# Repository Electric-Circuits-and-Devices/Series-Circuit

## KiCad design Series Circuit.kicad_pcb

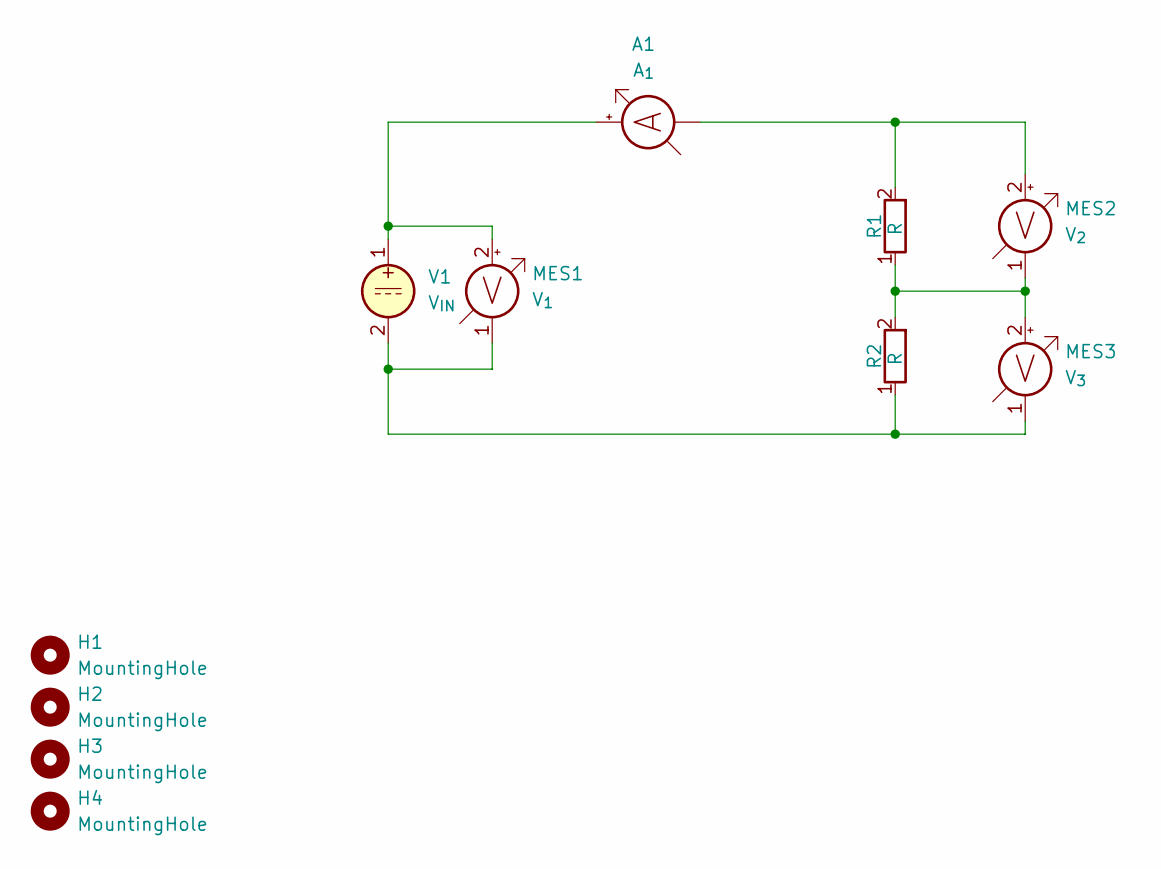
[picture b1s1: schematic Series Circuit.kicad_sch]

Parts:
A1: A_{1}; Ammeter horizontal
H1, H2, H3, H4: MountingHole; MountingHole_3.2mm_M3_Pad
MES1: V_{1}; Volt meter vertical
MES2: V_{2}; Volt meter vertical
MES3: V_{3}; Volt meter vertical
R1, R2: R; Resistor-Plugin_0.5Watt
V1: V_{IN}; DC Power Supply Vertical

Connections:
unnamed: A1.2 (+), MES1.2 (+), V1.1
unnamed: A1.1 (-), MES2.2 (+), R1.2
unnamed: MES1.1 (-), MES3.1 (-), R2.1, V1.2
unnamed: MES2.1 (-), MES3.2 (+), R1.1, R2.2

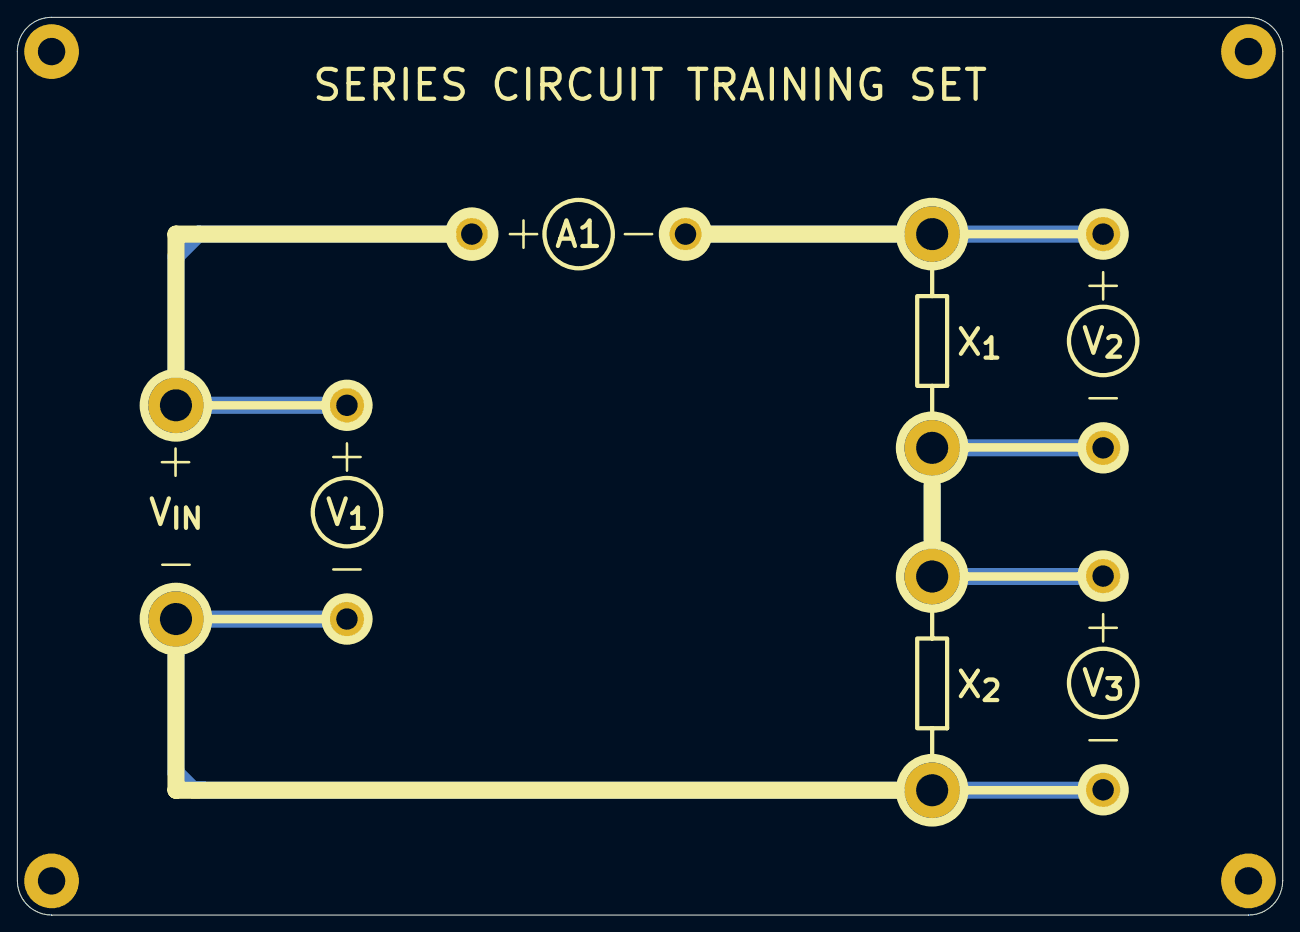
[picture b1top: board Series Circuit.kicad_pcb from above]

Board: 2 copper layers, 148.0 x 105.0 mm, 11 parts (0 on the bottom side), 4 nets.
